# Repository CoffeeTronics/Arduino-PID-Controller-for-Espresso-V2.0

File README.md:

Arduino-PID-Controller-for-Espresso-V2.0
========================================

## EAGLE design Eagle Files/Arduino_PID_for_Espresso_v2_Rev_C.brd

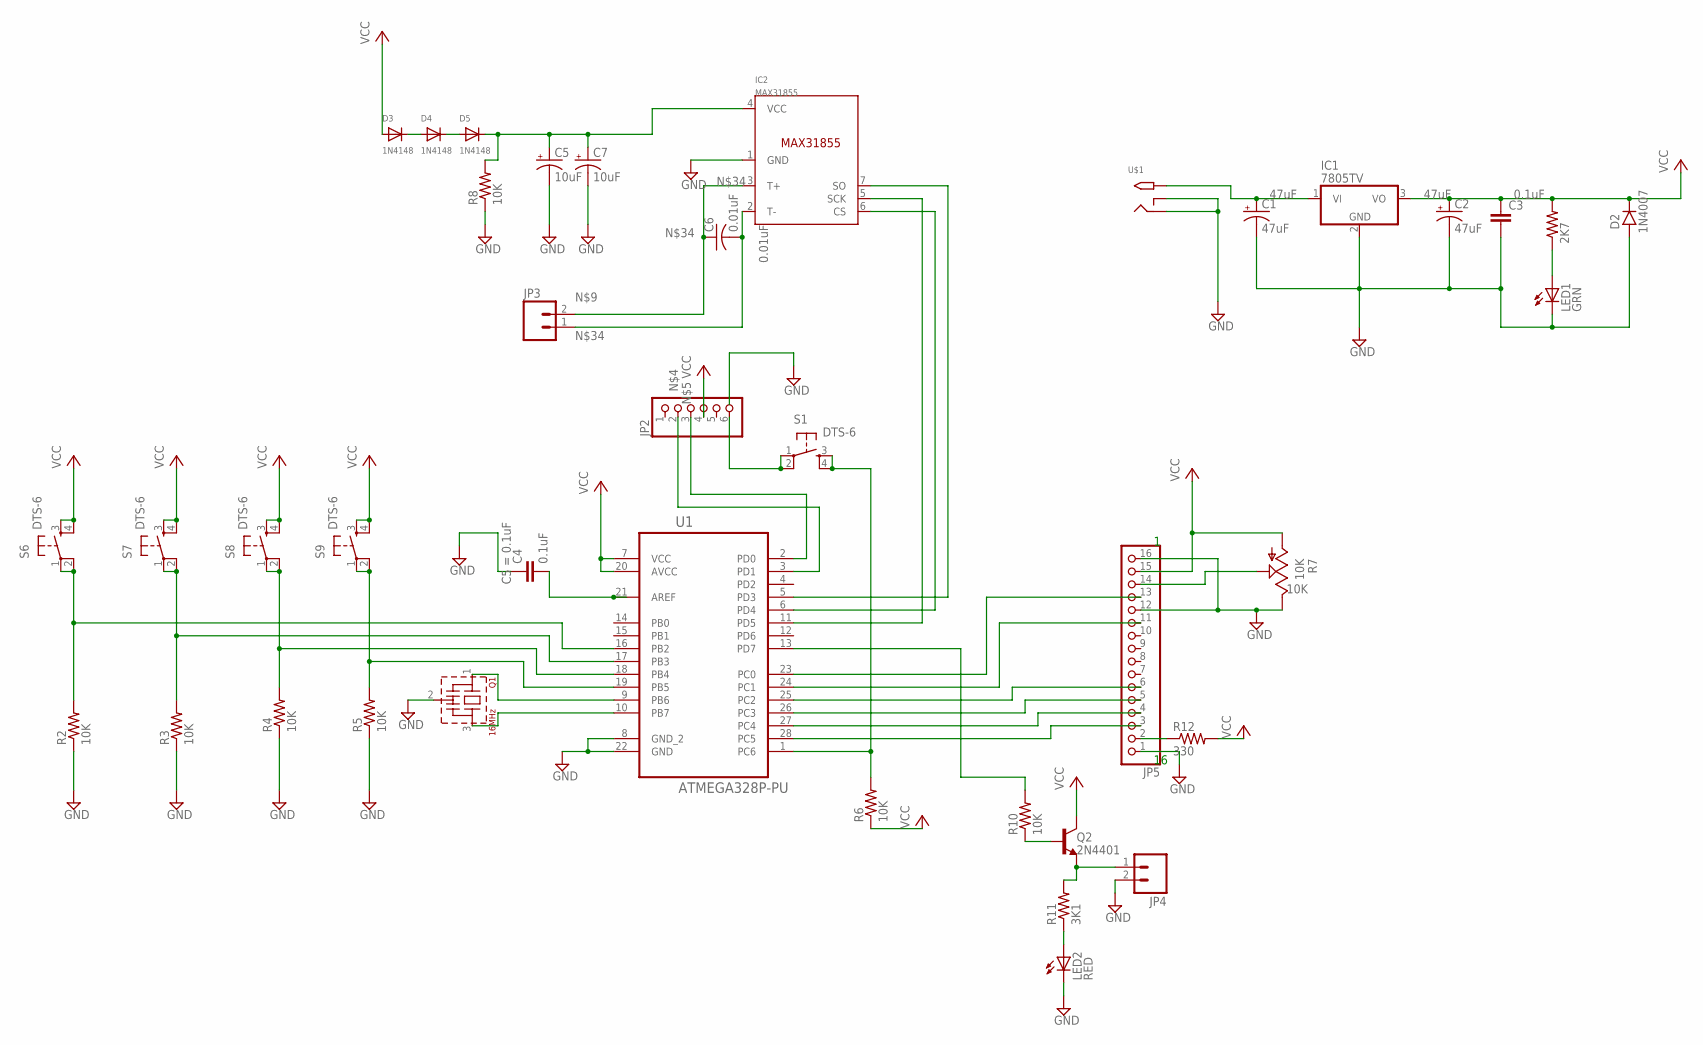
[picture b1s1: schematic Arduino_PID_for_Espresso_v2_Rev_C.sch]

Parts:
C1, C2: 47uF; TT5D6
C3: C-EU025-024X044; C025-024X044
C4: 0.1uF; C025-024X044
C5, C7: 10uF; CPOL-RADIAL-10UF-25V
C6: 0.01uF; C025-024X044
D2: 1N4007; DO41-3
D3, D4, D5: 1N4148; DO-1N4148
IC1: 7805TV; TO220V
IC2: MAX31855; SOIC8
JP2: PINHD-1X6/90; 1X06/90
JP3, JP4: M023.5MM; SCREWTERMINAL-3.5MM-2
JP5: PINHD-1X16; 1X16
LED1: GRN; LED3MM
LED2: RED; LED3MM
Q1: 16MHz; CSTLA_T
Q2: 2N4401; TO92-
R1: 2K7; AXIAL-0.4
R2, R3, R4, R5, R6, R8, R10: 10K; 1/6W-RES
R7: 10K; B25P
R11: 3K1; AXIAL-0.4
R12: 330; AXIAL-0.4
S1, S6, S7, S8, S9: DTS-6
U1: ATMEGA328P-PU; DIP254P762X457-28
U$1: 2.1MMJACKTHM; PJ-102A

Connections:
GND: C1.-, C2.-, C3.2, C4.1, C5.2 (-), C7.2 (-), D2.A, IC1.2 (GND), IC2.1 (GND), JP2.6, JP4.2, JP5.1, JP5.12, JP5.16, LED1.K (C), LED2.K (C), Q1.2 (VSS), R2.1, R3.1, R4.1, R5.1, R7.E, R8.1, S1.1, S1.2, U1.8 (GND_2), U1.22 (GND), U$1.RING, U$1.RING_SW
unnamed: C1.+, IC1.1 (VI), U$1.TIP
unnamed: C4.2, U1.21 (AREF)
unnamed: LED1.A, R1.P$1 (1)
unnamed: JP2.2, U1.3 (PD1)
unnamed: JP2.3, U1.2 (PD0)
unnamed: R2.2, S6.1, S6.2, U1.16 (PB2)
unnamed: JP5.14, R7.S
unnamed: JP5.2, R12.P$1 (1)
unnamed: C6.2, IC2.2 (T-), JP3.1
unnamed: R4.2, S8.1, S8.2, U1.18 (PB4)
unnamed: Q1.1, U1.9 (PB6)
unnamed: Q1.3, U1.10 (PB7)
unnamed: R6.2, S1.3, S1.4, U1.1 (PC6)
unnamed: R3.2, S7.1, S7.2, U1.17 (PB3)
unnamed: R5.2, S9.1, S9.2, U1.19 (PB5)
unnamed: JP5.3, U1.28 (PC5)
unnamed: JP5.4, U1.27 (PC4)
unnamed: IC2.6 (CS), U1.6 (PD4)
unnamed: JP5.5, U1.26 (PC3)
unnamed: IC2.7 (SO), U1.5 (PD3)
unnamed: IC2.5 (SCK), U1.11 (PD5)
unnamed: D3.C, D4.A
unnamed: D4.C, D5.A
unnamed: C5.1 (+), C7.1 (+), D5.C, IC2.4 (VCC), R8.2
unnamed: JP5.6, U1.25 (PC2)
unnamed: JP5.11, U1.24 (PC1)
unnamed: JP5.13, U1.23 (PC0)
unnamed: Q2.2 (B), R10.1
unnamed: JP4.1, Q2.3 (E), R11.P$2 (2)
unnamed: R10.2, U1.13 (PD7)
unnamed: LED2.A, R11.P$1 (1)
unnamed: C6.1, IC2.3 (T+), JP3.2
VCC: C2.+, C3.1, D2.C, D3.A, IC1.3 (VO), JP2.4, JP5.15, Q2.1 (C), R1.P$2 (2), R6.1, R7.A, R12.P$2 (2), S6.3, S6.4, S7.3, S7.4, S8.3, S8.4, S9.3, S9.4, U1.7 (VCC), U1.20 (AVCC)

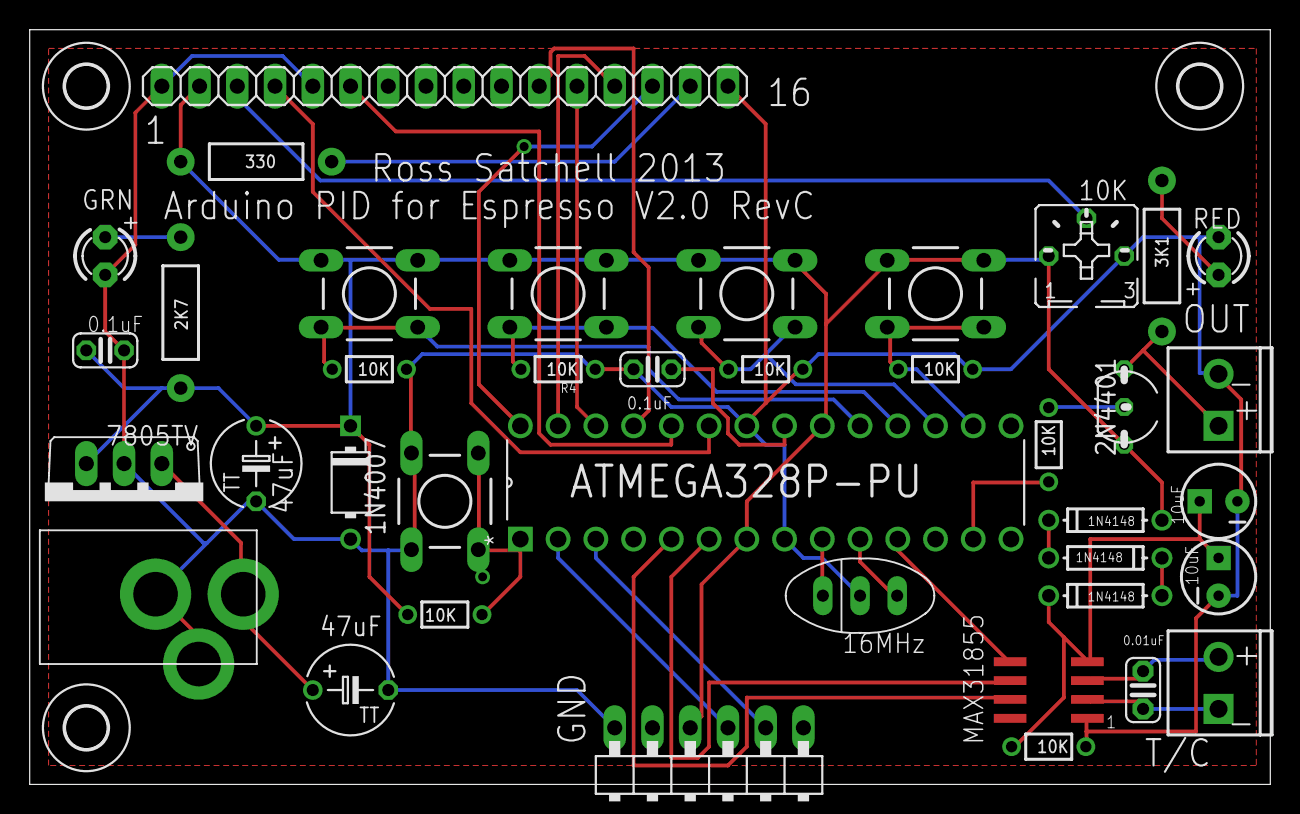
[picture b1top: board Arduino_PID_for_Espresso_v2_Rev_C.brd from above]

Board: 2 copper layers, 83.5 x 50.8 mm, 42 parts (0 on the bottom side), 34 nets.

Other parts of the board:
U$2, U$3, U$4: 2,8

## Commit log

2013-06-02 Initial upload for v2.0
2013-07-03 Added Eagle Schematic & PCB files
2020-07-11 Force correct placement of function prototypes
    The Arduino sketch preprocessor automatically generates function prototypes for any function in a .ino file that doesn't already have a prototype. This system usually works perfectly, but in some rar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
    It's likely that the function prototypes happened to be inserted at the correct location at the time this sketch was written. In the seven years since that time, Arduino has done a maj

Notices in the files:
parts and their libraries:
SparkFun-Connectors: Licensing: CC v3.0 Share-Alike You are welcome to use this library for commercial purposes.
